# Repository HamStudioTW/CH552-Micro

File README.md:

```                                                                     
  ╭──╮                        ╭──────────────────╮                  
  |  |                        |  ╭────────────╮  |        ╭──────────╮          
  |  │            ╭──╮        |  |            |  |        |  ╭────╮  ╰───────╮  
  |  ╰────────────╯  |        |  ╰────────────╯  |        |  |    |  ╭────╮  |  
  |  ╭────────────╮  |        |  ╭────────────╮  |        |  |    |  |    |  |  
  |  │            │  |        |  │            │  |        |  |    |  |    |  |  
  |  │            │  |        |  │            │  |        |  |    |  |    |  | 
  ╰──╯            ╰──╯        ╰──╯            ╰──╯        ╰──╯    ╰──╯    ╰──╯  Studio
```
# CH552-Micro

CH552 Micro is development board base on CH552G
This development board can use on Breadboard here will be three empty lines on the left and right

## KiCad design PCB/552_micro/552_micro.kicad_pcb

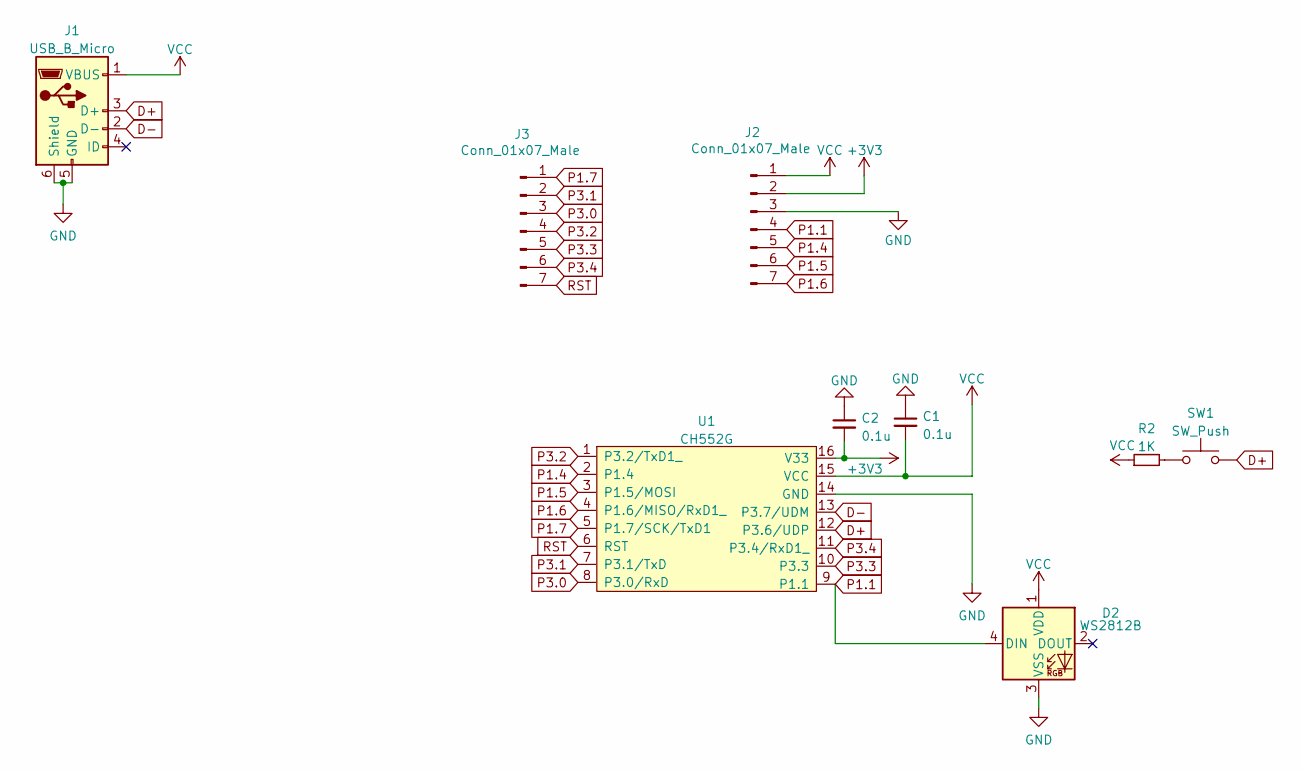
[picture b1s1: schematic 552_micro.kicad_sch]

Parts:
C1, C2: 0.1u; C_0805_2012Metric_Pad1.18x1.45mm_HandSolder
D2: WS2812B
J1: USB_B_Micro; USB_Micro-B_Amphenol_10118194_Horizontal
J2, J3: Conn_01x07_Male; PinHeader_1x07_P2.54mm_Vertical
R2: 1K; R_0805_2012Metric_Pad1.20x1.40mm_HandSolder
SW1: SW_Push; SW_Push_SPST_NO_Alps_SKRK
U1: CH552G; SOIC-16_4.55x10.3mm_P1.27mm

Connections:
+3V3: C2.2, J2.2, U1.16 (V33)
D+: J1.3 (D+), SW1.2, U1.12 (P3.6/UDP)
D-: J1.2 (D-), U1.13 (P3.7/UDM)
GND: C1.1, C2.1, D2.3 (VSS), J1.5 (GND), J1.6 (Shield), J2.3, U1.14 (GND)
unnamed: R2.2, SW1.1
P1.1: D2.4 (DIN), J2.4, U1.9 (P1.1)
P1.4: J2.5, U1.2 (P1.4)
P1.5: J2.6, U1.3 (P1.5/MOSI)
P1.6: J2.7, U1.4 (P1.6/MISO/RxD1_)
P1.7: J3.1, U1.5 (P1.7/SCK/TxD1)
P3.0: J3.3, U1.8 (P3.0/RxD)
P3.1: J3.2, U1.7 (P3.1/TxD)
P3.2: J3.4, U1.1 (P3.2/TxD1_)
P3.3: J3.5, U1.10 (P3.3)
P3.4: J3.6, U1.11 (P3.4/RxD1_)
RST: J3.7, U1.6 (RST)
VCC: C1.2, D2.1 (VDD), J1.1 (VBUS), J2.1, R2.1, U1.15 (VCC)

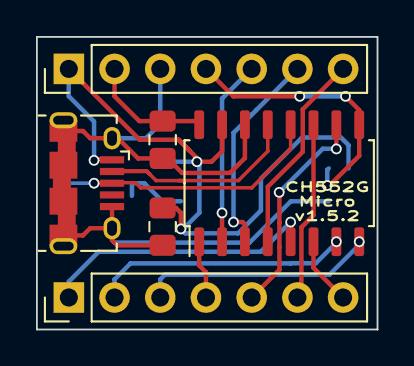
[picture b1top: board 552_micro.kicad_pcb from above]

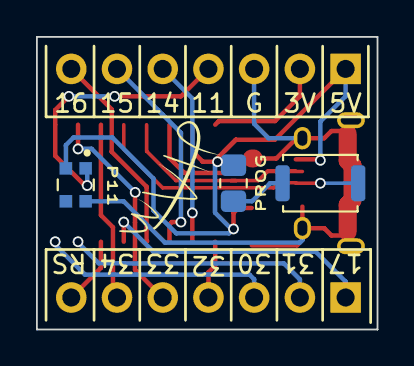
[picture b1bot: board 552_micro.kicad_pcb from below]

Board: 2 copper layers, 18.9 x 16.3 mm, 9 parts (3 on the bottom side), 17 nets.

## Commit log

2023-02-03 Add PCB
